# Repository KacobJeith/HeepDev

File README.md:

# Heep is Easier to Build, Install, and Use

This repository contains Circuit Board Eagle CAD Files, Server Code, OS Dependent Client Code, and Client Firmware for Heep devices.

Code written for this repository should aim to be testable, elegant, easy to understand, and robust.

## Dependencies

* Heep Server
	* Python 2.7
* Python Clients
	* Python 2.7
* Firmware Clients
	* Modified UIP_Ethernet Library found in Firmware/ArduinoLibrary
	* Teensyduino
* Front End
	* Node.js

## Running the Heep Server
1. Clone the repo
2. Open a terminal and navigate to the FrontEnd/FlowChart directory
3. Type `npm install` to install all front end dependencies
4. Type `npm run bs` to build and start the FlowChart
5. Open a terminal and navigate to the Server directory
6. Type `python TestPLCServer.py` to start the server that will listen to devices on the network
7. Connect Devices and view the front end by opening a web browser and going to your-IP:3001

## Running a Heep Client
1. Clone the repo
2. Open a terminal and navigate to a client in the ExampleDevices directory
3. Find the name of the .py file in the example device folder you chose
4. Type `Python device-name.py` in the terminal to start the client
5. The client should show up on the heep server front end

## What is a Heep Client

A Heep client is a named collection of inputs and outputs that communicate with other Heep clients over a line called a "Vertex." Every client contains these components.

* *Name*: The client's name is the word that humans use to identify the client
* *ID*: The ID is a unique number that is used by Heep to identify a client regardless of IP Address or MAC Address

## Heep General Architecture

### Software Design for Sending

### Software Design for Receiving

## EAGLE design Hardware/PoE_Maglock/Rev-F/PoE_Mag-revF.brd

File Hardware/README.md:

# Heep Hardware

Welcome to Heep hardware. This part of the Repo contains the Eagle Schematic and Layout files for the circuit board hardware that makes our system tick. The hardware you'll find in here is described below.

## Manufacturing Files

### [Seeed Design Files](Seeed Design Files/)

This section contains the CAM and DRC scripts required to prepare a circuit board under Seeed Studio's Fusion PCB Service. 

## Circuit Board Designs

### [Heep 32u4 Board](Heep32u4Board/)

This circuit runs an ATMega32u4 microprocessor along with a Microchip ENC28J60 ethernet controller to give its relays access to the Heep system. This is a potential candidate for the board behind a Heep Home smart plug or receptacle.

### [Heep Teensy Board](HeepTeensyBoard/)

This is a simple circuit that gives inexpensive network access to a Teensy. It simply holds a Teensy, breaks its pins out, and gives internet access to the Teensy.

### [Heep Teensy Board With Relays](HeepTeensyBoardWithRelays/) 

The same circuit as the Heep Teensy Board, but with 3 relays to allow smart plug and smart receptacle control. It also opens the doors to controlling any other high voltage or high current devices with Heep.

### [Heep Teensy Board With Relays Rev 2](HeepTeensyBoardWithRelaysRev2/) 

A more refined revision of the Teensy Relay board. This board more intelligently runs traces, and organizes the circuit components and connectors in a more accessible way.

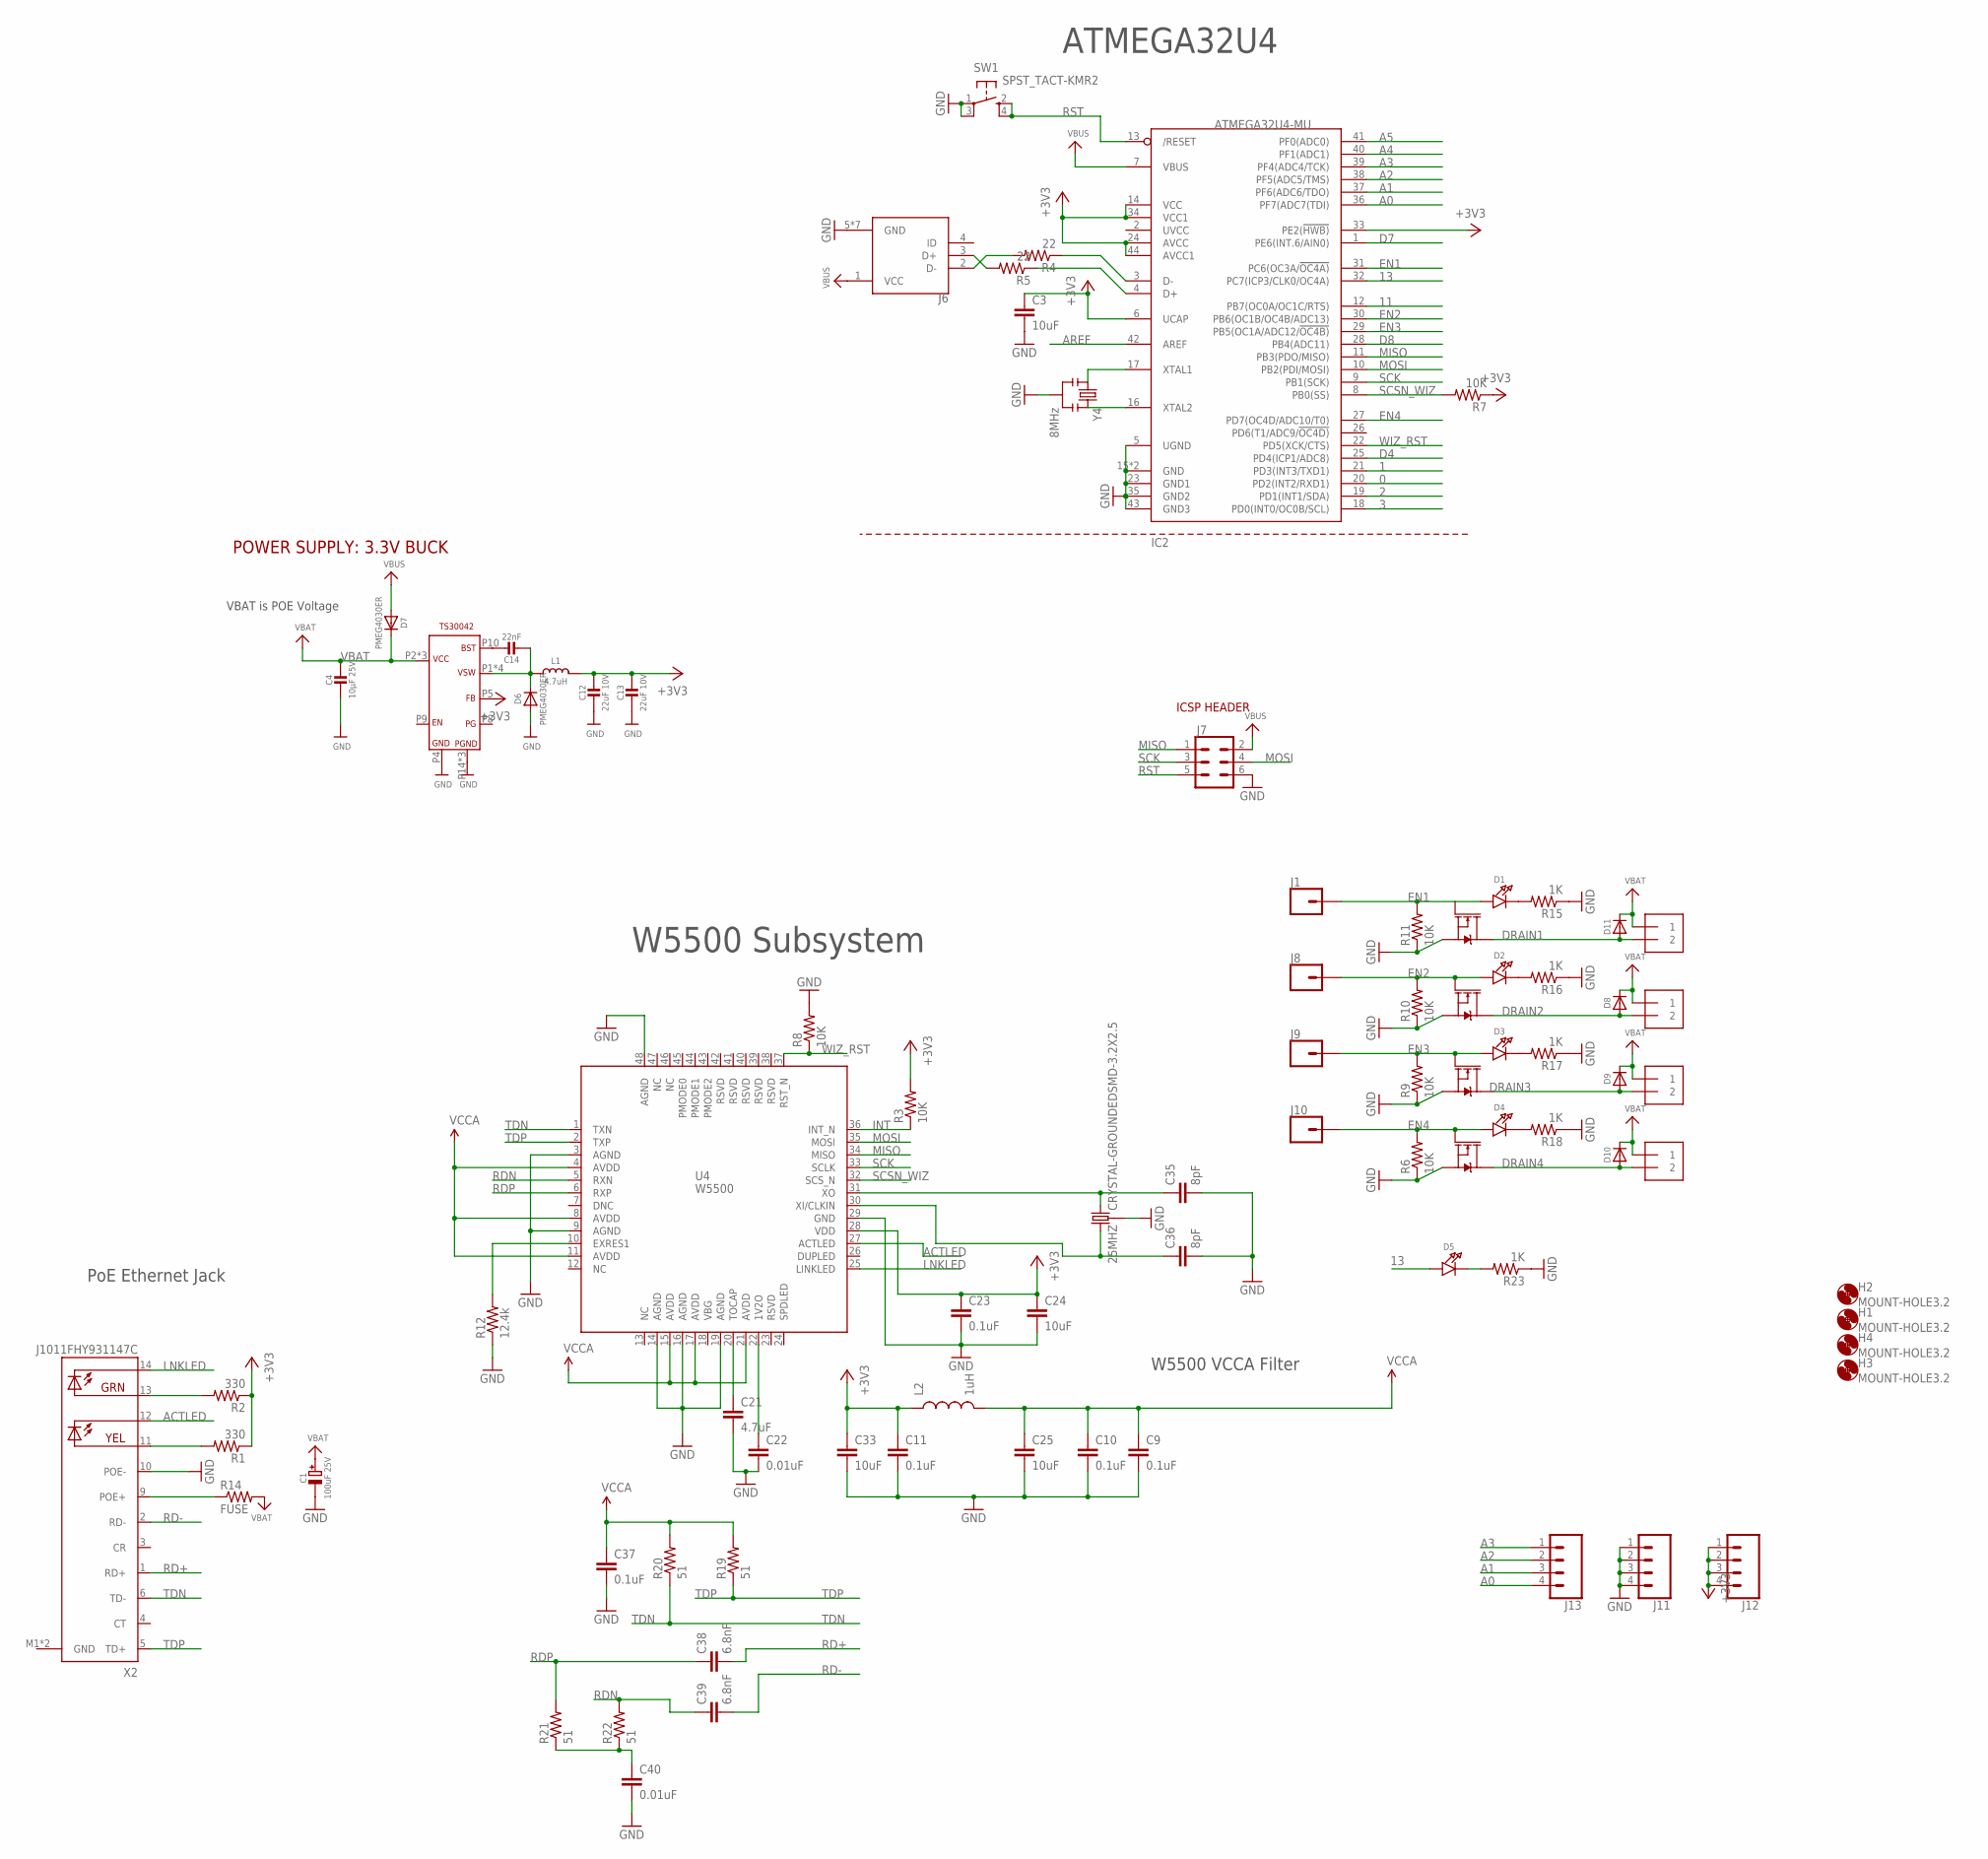
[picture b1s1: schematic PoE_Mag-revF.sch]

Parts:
25MHZ: CRYSTAL-GROUNDEDSMD-3.2X2.5; CRYSTAL-SMD-3.2X2.5MM
C1: 100uF 25V; PANASONIC_D
C3, C24, C25, C33: 10uF; 0603-CAP
C4: 10µF 25V; 0603-MINI
C9, C10, C11, C23, C37: 0.1uF; 0603-CAP
C12, C13: 22uF 10V; 0603-MINI
C14: 22nF; 0603-MINI
C21: 4.7uF; 0603-CAP
C22, C40: 0.01uF; 0603-CAP
C35, C36: 8pF; 0603-CAP
C38, C39: 6.8nF; 0603-CAP
D1, D2, D3, D4, D5: LED0805_NOOUTLINE; CHIPLED_0805_NOOUTLINE
D6, D7: PMEG4030ER; SOD-123
D8, D9, D10, D11: DIODESOD-123; SOD-123
H1, H2, H3, H4: MOUNT-HOLE3.2; 3,2
IC2: ATMEGA32U4-MU; TQFN44_7MM
J1, J8, J9, J10: CONN_01; 1X01
J2, J3, J4, J5: 1X2-3.5MM
J6: 10103594-0001LF; FCI_10103594-0001LF
J7: CONN_03X2NO_SILK; 2X3-NS
J11, J12: CONN_04; 1X04
J13: CONN_041X04_NO_SILK; 1X04_NO_SILK
L1: 4.7uH; INDUCTOR_5X5MM_TDK_VLC5045
L2: 1uH; 0603
Q1, Q3, Q5, Q6: 35A/25V/8.5mΩ; DPAK
R1, R2: 330; 0603-RES
R3, R6, R7, R8, R9, R10, R11: 10K; 0603-RES
R4, R5: 22; 0603-RES
R12: 12.4k; 0603-RES
R14: FUSE; 0603-RES
R15, R16, R17, R18, R23: 1K; 0603-RES
R19, R20, R21, R22: 51; 0603-RES
SW1: SPST_TACT-KMR2; KMR2
U4: W5500
U$19: BUCK_CONVERTER; QFN-16
X2: J1011FHY931147C; HANRUN_POE
Y4: 8MHz; RESONATOR-SMD

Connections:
0: IC2.20 (PD2(INT2/RXD1))
1: IC2.21 (PD3(INT3/TXD1))
2: IC2.19 (PD1(INT1/SDA))
3: IC2.18 (PD0(INT0/OC0B/SCL))
11: IC2.12 (PB7(OC0A/OC1C/RTS))
13: D5.A, IC2.32 (PC7(ICP3/CLK0/OC4A))
+3V3: C3.1, C11.1, C12.1, C13.1, C23.1, C24.1, C33.1, IC2.6 (UCAP), IC2.14 (VCC), IC2.24 (AVCC), IC2.33 (PE2(!HWB)), IC2.34 (VCC1), IC2.44 (AVCC1), J12.1, J12.2, J12.3, J12.4, L1.P$2 (2), L2.1, R1.1, R2.1, R3.2, R7.1, U4.28 (VDD), U$19.P5 (FB)
A0: IC2.36 (PF7(ADC7(TDI)), J13.4
A1: IC2.37 (PF6(ADC6/TDO)), J13.3
A2: IC2.38 (PF5(ADC5/TMS)), J13.2
A3: IC2.39 (PF4(ADC4/TCK)), J13.1
A4: IC2.40 (PF1(ADC1))
A5: IC2.41 (PF0(ADC0))
ACTLED: U4.27 (ACTLED), X2.12 (YEL-C)
AREF: IC2.42 (AREF)
D4: IC2.25 (PD4(ICP1/ADC8))
D7: IC2.1 (PE6(INT.6/AIN0))
D8: IC2.28 (PB4(ADC11))
D+: IC2.4 (D+), R5.1
D-: IC2.3 (D-), R4.1
DRAIN1: D11.A, J2.2, Q1.4 (D)
DRAIN2: D8.A, J3.2, Q3.4 (D)
DRAIN3: D9.A, J4.2, Q5.4 (D)
DRAIN4: D10.A, J5.2, Q6.4 (D)
EN1: D1.A, IC2.31 (PC6(OC3A/!OC4A)), J1.1, Q1.1 (G), R11.2
EN2: D2.A, IC2.30 (PB6(OC1B/OC4B/ADC13)), J8.1, Q3.1 (G), R10.2
EN3: D3.A, IC2.29 (PB5(OC1A/ADC12/!OC4B)), J9.1, Q5.1 (G), R9.2
EN4: D4.A, IC2.27 (PD7(OC4D/ADC10/T0)), J10.1, Q6.1 (G), R6.2
GND: 25MHZ.2 (3), 25MHZ.4 (3), C1.-, C3.2, C4.2, C9.2, C10.2, C11.2, C12.2, C13.2, C21.2, C22.2, C23.2, C24.2, C25.2, C33.2, C35.2, C36.2, C37.2, C40.2, D6.A, IC2.5 (UGND), IC2.15 (GND), IC2.23 (GND1), IC2.35 (GND2), IC2.43 (GND3), IC2.THERMAL (GND), J6.5 (GND), J6.P1 (GND), J6.P2 (GND), J6.P3 (GND), J6.P4 (GND), J6.P5 (GND), J6.P6 (GND), J7.6, J11.1, J11.2, J11.3, J11.4, Q1.3 (S), Q3.3 (S), Q5.3 (S), Q6.3 (S), R6.1, R8.2, R9.1, R10.1, R11.1, R12.1, R15.1, R16.1, R17.1, R18.1, R23.1, SW1.1, SW1.3 (P1), U4.3 (AGND), U4.9 (AGND), U4.14 (AGND), U4.16 (AGND), U4.19 (AGND), U4.29 (GND), U4.48 (AGND), U$19.P4 (GND), U$19.P14 (PGND), U$19.P15 (PGND), U$19.PAD (PGND), X2.10 (POE-), X2.M1 (GND), X2.M2 (GND), Y4.2
INT: R3.1, U4.36 (INT_N)
LNKLED: U4.25 (LINKLED), X2.14 (GRN-C)
MISO: IC2.11 (PB3(PDO/MISO)), J7.1, U4.34 (MISO)
MOSI: IC2.10 (PB2(PDI/MOSI)), J7.4, U4.35 (MOSI)
unnamed: R14.1, X2.9 (POE+)
unnamed: R2.2, X2.13 (GRN-A)
unnamed: R1.2, X2.11 (YEL-A)
unnamed: D1.C, R15.2
unnamed: J6.3 (D+), R5.2
unnamed: D2.C, R16.2
unnamed: D3.C, R17.2
unnamed: D4.C, R18.2
unnamed: D5.C, R23.2
unnamed: IC2.16 (XTAL2), Y4.3
unnamed: IC2.17 (XTAL1), Y4.1
unnamed: J6.2 (D-), R4.2
unnamed: C14.1, U$19.P10 (BST)
unnamed: C14.2, D6.C, L1.P$1 (1), U$19.P1 (VSW), U$19.P12 (VSW), U$19.P13 (VSW), U$19.P16 (VSW)
unnamed: C21.1, U4.20 (TOCAP)
unnamed: C22.1, U4.22 (1V2O)
unnamed: R12.2, U4.10 (EXRES1)
unnamed: C40.1, R21.1, R22.1
unnamed: 25MHZ.3 (2), C35.1, U4.31 (XO)
unnamed: 25MHZ.1, C36.1, U4.30 (XI/CLKIN)
RD+: C38.2, X2.1 (RD+)
RD-: C39.2, X2.2 (RD-)
RDN: C39.1, R22.2, U4.5 (RXN)
RDP: C38.1, R21.2, U4.6 (RXP)
RST: IC2.13 (/RESET), J7.5, SW1.2 (S), SW1.4 (S1)
SCK: IC2.9 (PB1(SCK)), J7.3, U4.33 (SCLK)
SCSN_WIZ: IC2.8 (PB0(SS)), R7.2, U4.32 (SCS_N)
TDN: R20.1, U4.1 (TXN), X2.6 (TD-)
TDP: R19.1, U4.2 (TXP), X2.5 (TD+)
VBAT: C1.+, C4.1, D7.C, D8.C, D9.C, D10.C, D11.C, J2.1, J3.1, J4.1, J5.1, R14.2, U$19.P2 (VCC), U$19.P3 (VCC), U$19.P11 (VCC)
VBUS: D7.A, IC2.7 (VBUS), J6.1 (VCC), J7.2
VCCA: C9.1, C10.1, C25.1, C37.1, L2.2, R19.2, R20.2, U4.4 (AVDD), U4.8 (AVDD), U4.11 (AVDD), U4.15 (AVDD), U4.17 (AVDD), U4.21 (AVDD)
WIZ_RST: IC2.22 (PD5(XCK/CTS)), R8.1, U4.37 (RST_N)

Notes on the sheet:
W5500 Subsystem
W5500 VCCA Filter
PoE Ethernet Jack
ATMEGA32U4
ICSP HEADER
POWER SUPPLY: 3.3V BUCK
VBAT is POE Voltage

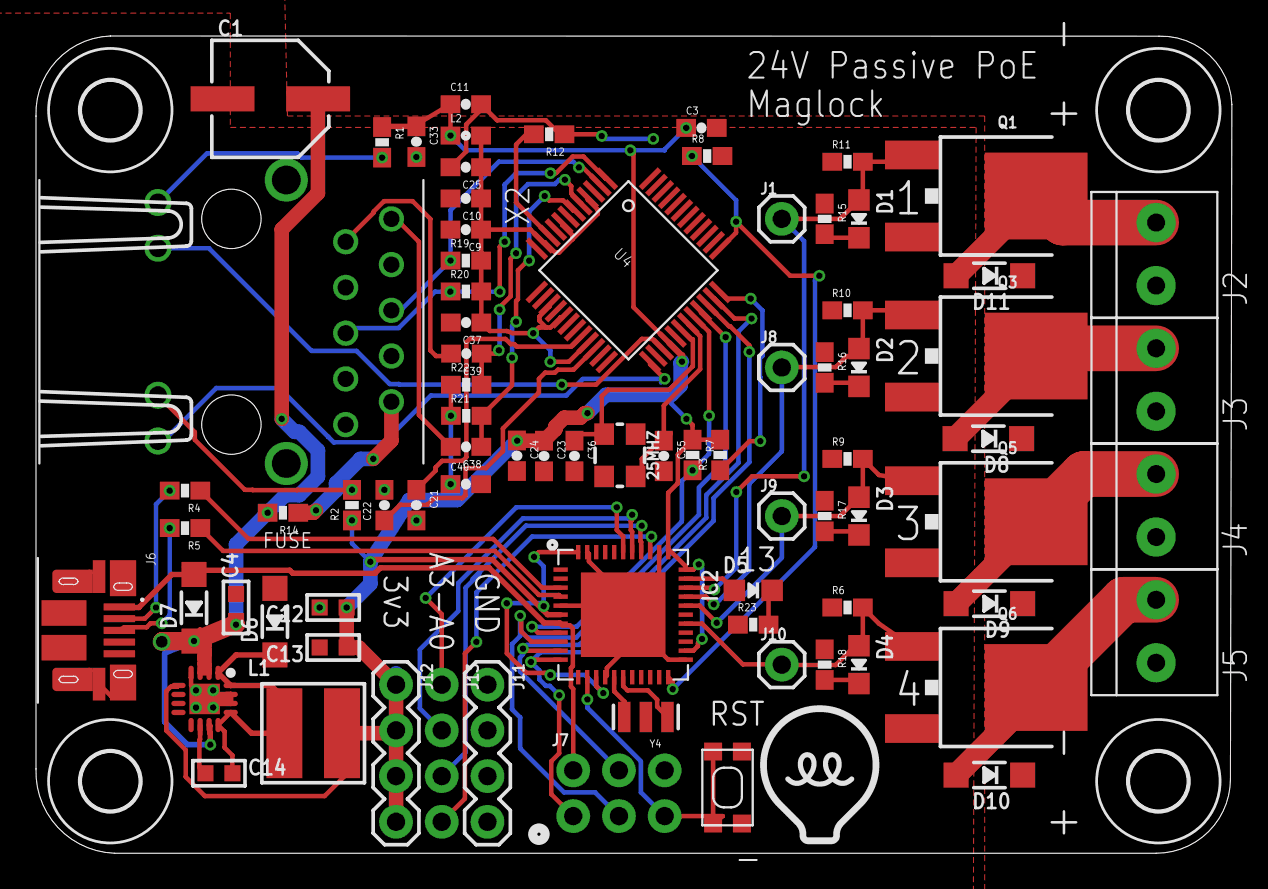
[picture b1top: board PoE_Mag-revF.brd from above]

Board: 2 copper layers, 66.4 x 45.4 mm, 85 parts (0 on the bottom side), 55 nets.

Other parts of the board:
U$15: HEEPLOGOSMALL

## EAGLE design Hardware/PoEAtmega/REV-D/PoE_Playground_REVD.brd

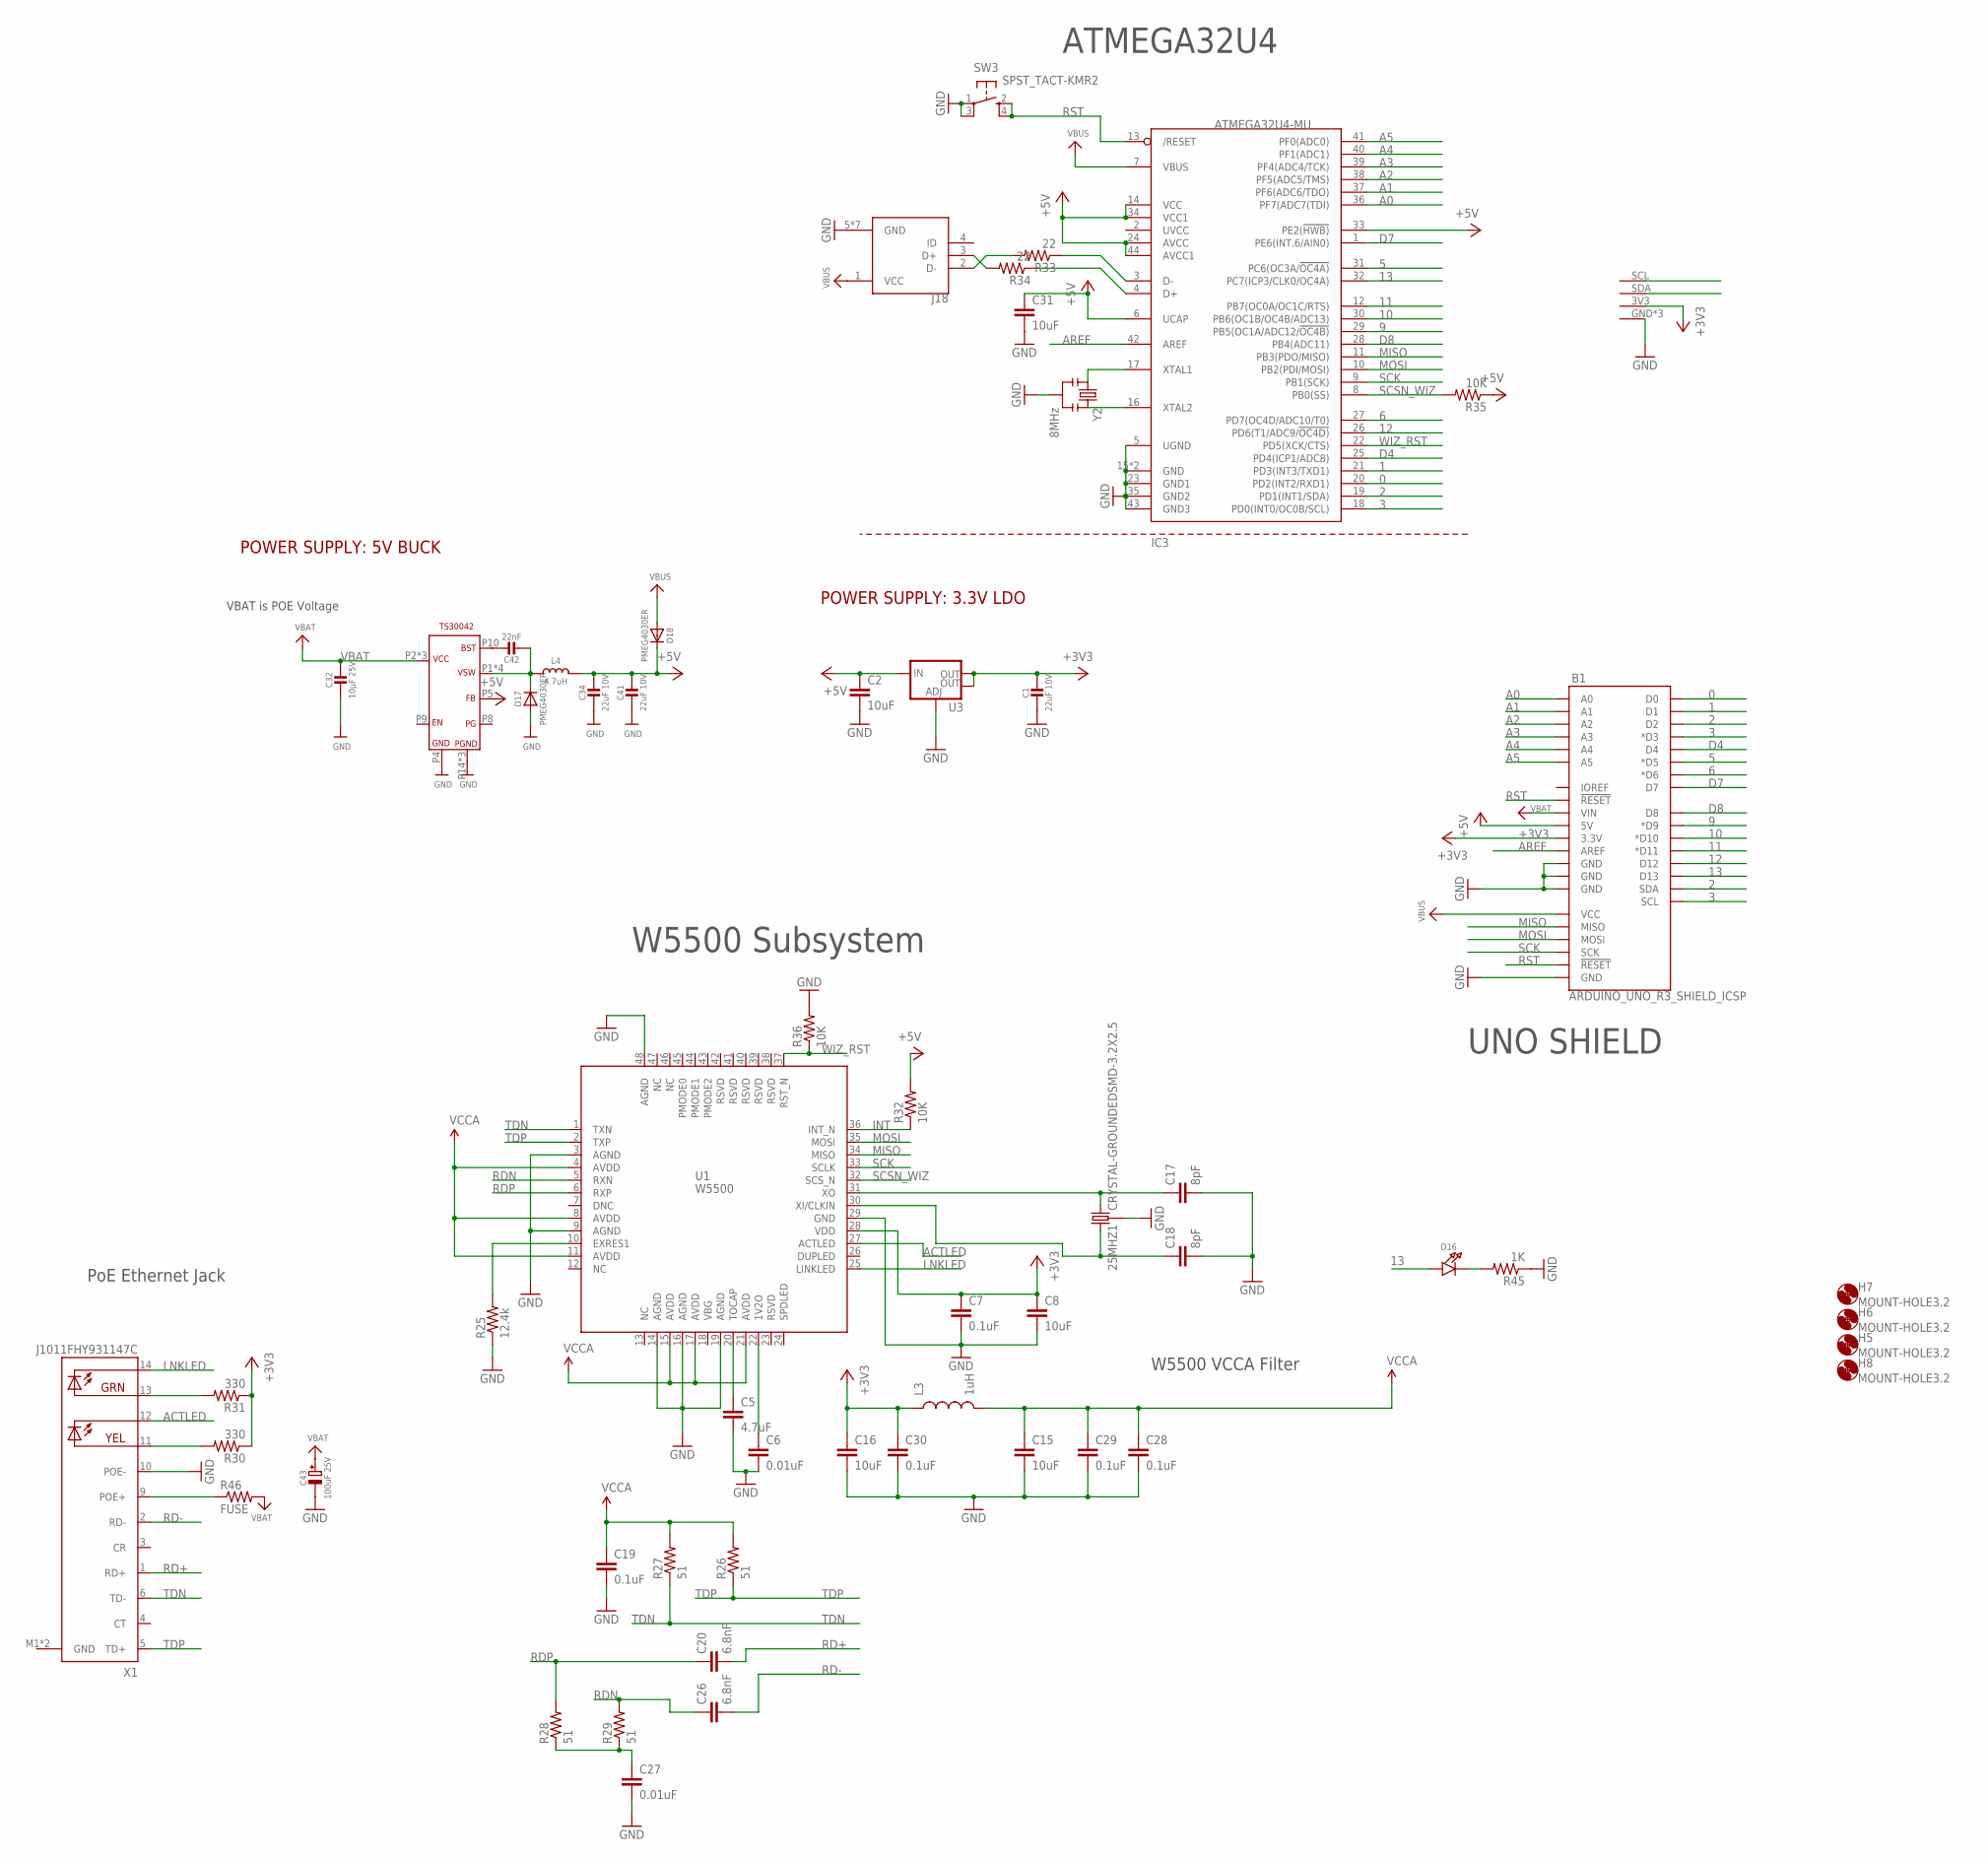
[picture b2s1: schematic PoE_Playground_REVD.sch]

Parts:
25MHZ1: CRYSTAL-GROUNDEDSMD-3.2X2.5; CRYSTAL-SMD-3.2X2.5MM
+5V_TS30042: BUCK_CONVERTER; QFN-16
B1: ARDUINO_UNO_R3_SHIELD_ICSP; UNO_R3_SHIELD_ICSP
C1, C34, C41: 22uF 10V; 0603-MINI
C2, C8, C15, C16, C31: 10uF; 0603-CAP
C5: 4.7uF; 0603-CAP
C6, C27: 0.01uF; 0603-CAP
C7, C19, C28, C29, C30: 0.1uF; 0603-CAP
C17, C18: 8pF; 0603-CAP
C20, C26: 6.8nF; 0603-CAP
C32: 10µF 25V; 0603-MINI
C42: 22nF; 0603-MINI
C43: 100uF 25V; PANASONIC_D
D16: LED0805_NOOUTLINE; CHIPLED_0805_NOOUTLINE
D17, D18: PMEG4030ER; SOD-123
H5, H6, H7, H8: MOUNT-HOLE3.2; 3,2
IC3: ATMEGA32U4-MU; TQFN44_7MM
J18: 10103594-0001LF; FCI_10103594-0001LF
L3: 1uH; 0603
L4: 4.7uH; INDUCTOR_5X5MM_TDK_VLC5045
R25: 12.4k; 0603-RES
R26, R27, R28, R29: 51; 0603-RES
R30, R31: 330; 0603-RES
R32, R35, R36: 10K; 0603-RES
R33, R34: 22; 0603-RES
R45: 1K; 0603-RES
R46: FUSE; 0603-RES
SW3: SPST_TACT-KMR2; KMR2
U1: W5500
U3: V_REG_LM1117SOT223; SOT223
U$3: 4P_JST_MINI_MICRO; 4P_JST1.0
X1: J1011FHY931147C; HANRUN_POE
Y2: 8MHz; RESONATOR-SMD

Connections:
0: B1.RX (D0), IC3.20 (PD2(INT2/RXD1))
1: B1.TX (D1), IC3.21 (PD3(INT3/TXD1))
2: B1.D2, B1.SDA, IC3.19 (PD1(INT1/SDA)), U$3.SDA
3: B1.D3 (*D3), B1.SCL, IC3.18 (PD0(INT0/OC0B/SCL)), U$3.SCL
5: B1.D5 (*D5), IC3.31 (PC6(OC3A/!OC4A))
6: B1.D6 (*D6), IC3.27 (PD7(OC4D/ADC10/T0))
9: B1.D9 (*D9), IC3.29 (PB5(OC1A/ADC12/!OC4B))
10: B1.D10 (*D10), IC3.30 (PB6(OC1B/OC4B/ADC13))
11: B1.D11 (*D11), IC3.12 (PB7(OC0A/OC1C/RTS))
12: B1.D12, IC3.26 (PD6(T1/ADC9/!OC4D))
13: B1.D13, D16.A, IC3.32 (PC7(ICP3/CLK0/OC4A))
+3V3: B1.3.3V, C1.1, C7.1, C8.1, C16.1, C30.1, L3.1, R30.1, R31.1, U1.28 (VDD), U3.2 (OUT), U3.4 (OUT), U$3.3V3
+5V: +5V_TS30042.P5 (FB), B1.5V, C2.1, C31.1, C34.1, C41.1, D18.C, IC3.6 (UCAP), IC3.14 (VCC), IC3.24 (AVCC), IC3.33 (PE2(!HWB)), IC3.34 (VCC1), IC3.44 (AVCC1), L4.P$2 (2), R32.2, R35.1, U3.3 (IN)
A0: B1.A0, IC3.36 (PF7(ADC7(TDI))
A1: B1.A1, IC3.37 (PF6(ADC6/TDO))
A2: B1.A2, IC3.38 (PF5(ADC5/TMS))
A3: B1.A3, IC3.39 (PF4(ADC4/TCK))
A4: B1.A4, IC3.40 (PF1(ADC1))
A5: B1.A5, IC3.41 (PF0(ADC0))
ACTLED: U1.27 (ACTLED), X1.12 (YEL-C)
AREF: B1.AREF, IC3.42 (AREF)
D4: B1.D4, IC3.25 (PD4(ICP1/ADC8))
D7: B1.D7, IC3.1 (PE6(INT.6/AIN0))
D8: B1.D8, IC3.28 (PB4(ADC11))
D+2: IC3.4 (D+), R34.1
D-2: IC3.3 (D-), R33.1
GND: 25MHZ1.2 (3), 25MHZ1.4 (3), +5V_TS30042.P4 (GND), +5V_TS30042.P14 (PGND), +5V_TS30042.P15 (PGND), +5V_TS30042.PAD (PGND), B1.GND@0 (GND), B1.GND@1 (GND), B1.GND@2 (GND), B1.GND_ICSP (GND), C1.2, C2.2, C5.2, C6.2, C7.2, C8.2, C15.2, C16.2, C17.2, C18.2, C19.2, C27.2, C28.2, C29.2, C30.2, C31.2, C32.2, C34.2, C41.2, C43.-, D17.A, IC3.5 (UGND), IC3.15 (GND), IC3.23 (GND1), IC3.35 (GND2), IC3.43 (GND3), IC3.THERMAL (GND), J18.5 (GND), J18.P1 (GND), J18.P2 (GND), J18.P3 (GND), J18.P4 (GND), J18.P5 (GND), J18.P6 (GND), R25.1, R36.2, R45.1, SW3.1, SW3.3 (P1), U1.3 (AGND), U1.9 (AGND), U1.14 (AGND), U1.16 (AGND), U1.19 (AGND), U1.29 (GND), U1.48 (AGND), U3.1 (ADJ), U$3.GND, U$3.P$4 (GND), U$3.P$5 (GND), X1.10 (POE-), X1.M1 (GND), X1.M2 (GND), Y2.2
INT: R32.1, U1.36 (INT_N)
LNKLED: U1.25 (LINKLED), X1.14 (GRN-C)
MISO: B1.MISO, IC3.11 (PB3(PDO/MISO)), U1.34 (MISO)
MOSI: B1.MOSI, IC3.10 (PB2(PDI/MOSI)), U1.35 (MOSI)
unnamed: C5.1, U1.20 (TOCAP)
unnamed: C6.1, U1.22 (1V2O)
unnamed: R25.2, U1.10 (EXRES1)
unnamed: C27.1, R28.1, R29.1
unnamed: 25MHZ1.3 (2), C17.1, U1.31 (XO)
unnamed: 25MHZ1.1, C18.1, U1.30 (XI/CLKIN)
unnamed: IC3.16 (XTAL2), Y2.3
unnamed: IC3.17 (XTAL1), Y2.1
unnamed: J18.3 (D+), R34.2
unnamed: J18.2 (D-), R33.2
unnamed: D16.C, R45.2
unnamed: R31.2, X1.13 (GRN-A)
unnamed: R30.2, X1.11 (YEL-A)
unnamed: +5V_TS30042.P10 (BST), C42.1
unnamed: +5V_TS30042.P1 (VSW), +5V_TS30042.P12 (VSW), +5V_TS30042.P13 (VSW), +5V_TS30042.P16 (VSW), C42.2, D17.C, L4.P$1 (1)
unnamed: R46.1, X1.9 (POE+)
RD+: C20.2, X1.1 (RD+)
RD-: C26.2, X1.2 (RD-)
RDN: C26.1, R29.2, U1.5 (RXN)
RDP: C20.1, R28.2, U1.6 (RXP)
RST: B1.RES (!RESET!), B1.RST_ICSP (!RESET!), IC3.13 (/RESET), SW3.2 (S), SW3.4 (S1)
SCK: B1.SCK, IC3.9 (PB1(SCK)), U1.33 (SCLK)
SCSN_WIZ: IC3.8 (PB0(SS)), R35.2, U1.32 (SCS_N)
TDN: R27.1, U1.1 (TXN), X1.6 (TD-)
TDP: R26.1, U1.2 (TXP), X1.5 (TD+)
VBAT: +5V_TS30042.P2 (VCC), +5V_TS30042.P3 (VCC), +5V_TS30042.P11 (VCC), B1.VIN, C32.1, C43.+, R46.2
VBUS: B1.5V_ICSP (VCC), D18.A, IC3.7 (VBUS), J18.1 (VCC)
VCCA: C15.1, C19.1, C28.1, C29.1, L3.2, R26.2, R27.2, U1.4 (AVDD), U1.8 (AVDD), U1.11 (AVDD), U1.15 (AVDD), U1.17 (AVDD), U1.21 (AVDD)
WIZ_RST: IC3.22 (PD5(XCK/CTS)), R36.1, U1.37 (RST_N)

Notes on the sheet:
UNO SHIELD
W5500 Subsystem
W5500 VCCA Filter
PoE Ethernet Jack
ATMEGA32U4
POWER SUPPLY: 5V BUCK
VBAT is POE Voltage
POWER SUPPLY: 3.3V LDO

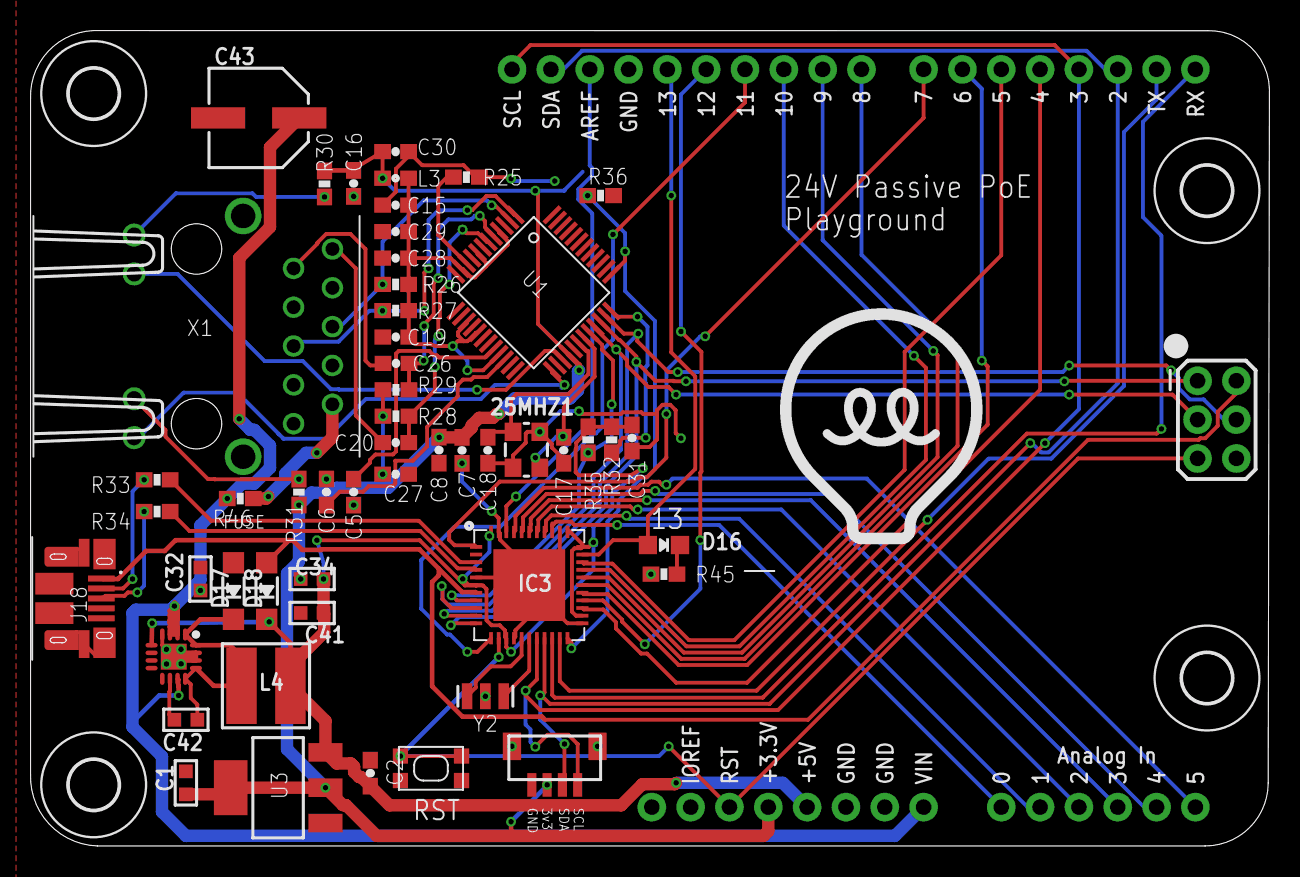
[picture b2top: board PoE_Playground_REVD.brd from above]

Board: 2 copper layers, 81.0 x 53.3 mm, 58 parts (0 on the bottom side), 60 nets.

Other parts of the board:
U$2: HEEPLOGO

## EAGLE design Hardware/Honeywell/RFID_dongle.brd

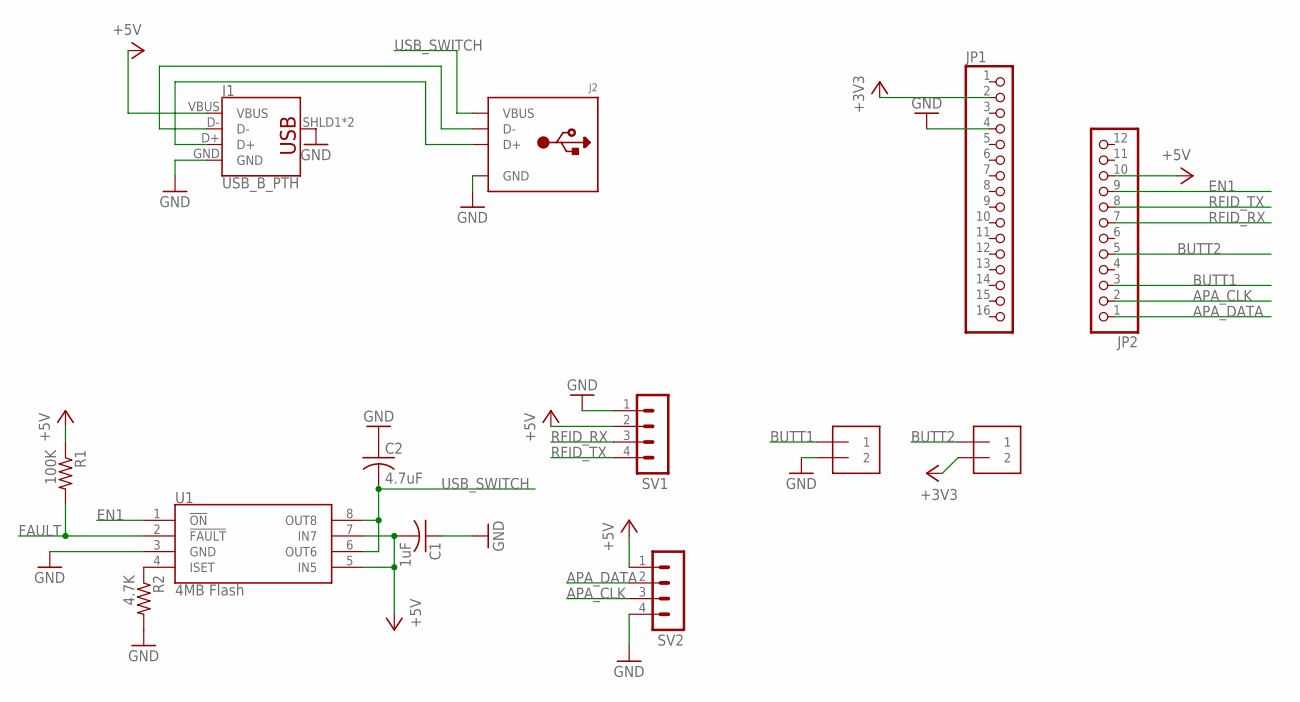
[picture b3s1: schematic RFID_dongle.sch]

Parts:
C1: 1uF; C0805K
C2: 4.7uF; C0805K
J1: USB_B_PTH; USB-B-PTH
J2: USB_TYPEAPTHFML; USB_HOST-PTH
J5, J6: 1X2-3.5MM
JP1: HEADER-1X16_MIN; 1X16_ROUND_MIN
JP2: HEADER-1X12_MIN; 1X12_ROUND_MIN
R1: 100K; R0805
R2: 4.7K; R0805
SV1, SV2: MA04-1
U1: 4MB Flash; SO08

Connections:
+3V3: J6.2, JP1.2
+5V: C1.2, J1.VBUS, JP2.10, R1.1, SV1.2, SV2.1, U1.5 (IN5), U1.7 (IN7)
APA_CLK: JP2.2, SV2.3
APA_DATA: JP2.1, SV2.2
BUTT1: J5.1, JP2.3
BUTT2: J6.1, JP2.5
EN1: JP2.9, U1.1 (!ON)
FAULT: R1.2, U1.2 (!FAULT)
GND: C1.1, C2.1, J1.GND, J1.SHLD1 (SHIELD), J1.SHLD2 (SHIELD), J2.GND, J2.S1 (GND), J2.S2 (GND), J5.2, JP1.4, R2.2, SV1.1, SV2.4, U1.3 (GND)
unnamed: R2.1, U1.4 (ISET)
unnamed: J1.D-, J2.D-
unnamed: J1.D+, J2.D+
RFID_RX: JP2.7, SV1.3
RFID_TX: JP2.8, SV1.4
USB_SWITCH: C2.2, J2.VBUS, U1.6 (OUT6), U1.8 (OUT8)

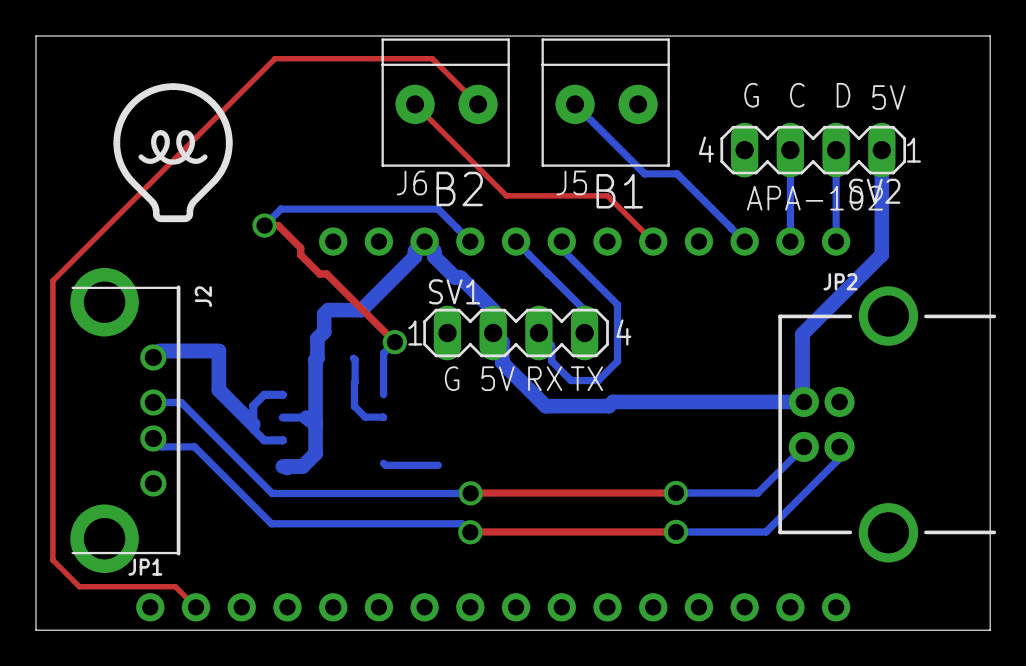
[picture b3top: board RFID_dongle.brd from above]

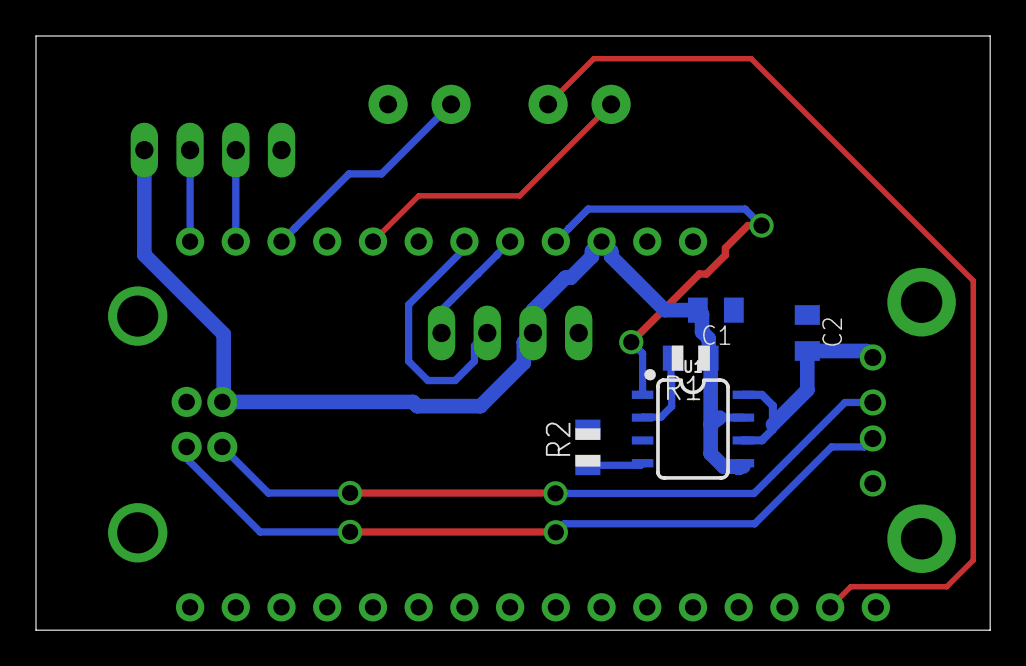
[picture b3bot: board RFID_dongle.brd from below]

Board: 2 copper layers, 53.0 x 33.0 mm, 14 parts (5 on the bottom side), 15 nets.

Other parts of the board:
U$1: HEEPLOGOSMALL

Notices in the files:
parts and their libraries:
microbuilder: This work is placed in the public domain, and may be freely used for commercial and non-commercial work with the following conditions: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
SparkFun-Connectors: Licensing: Creative Commons ShareAlike 4.0 International - https://creativecommons.org/licenses/by-sa/4.0
